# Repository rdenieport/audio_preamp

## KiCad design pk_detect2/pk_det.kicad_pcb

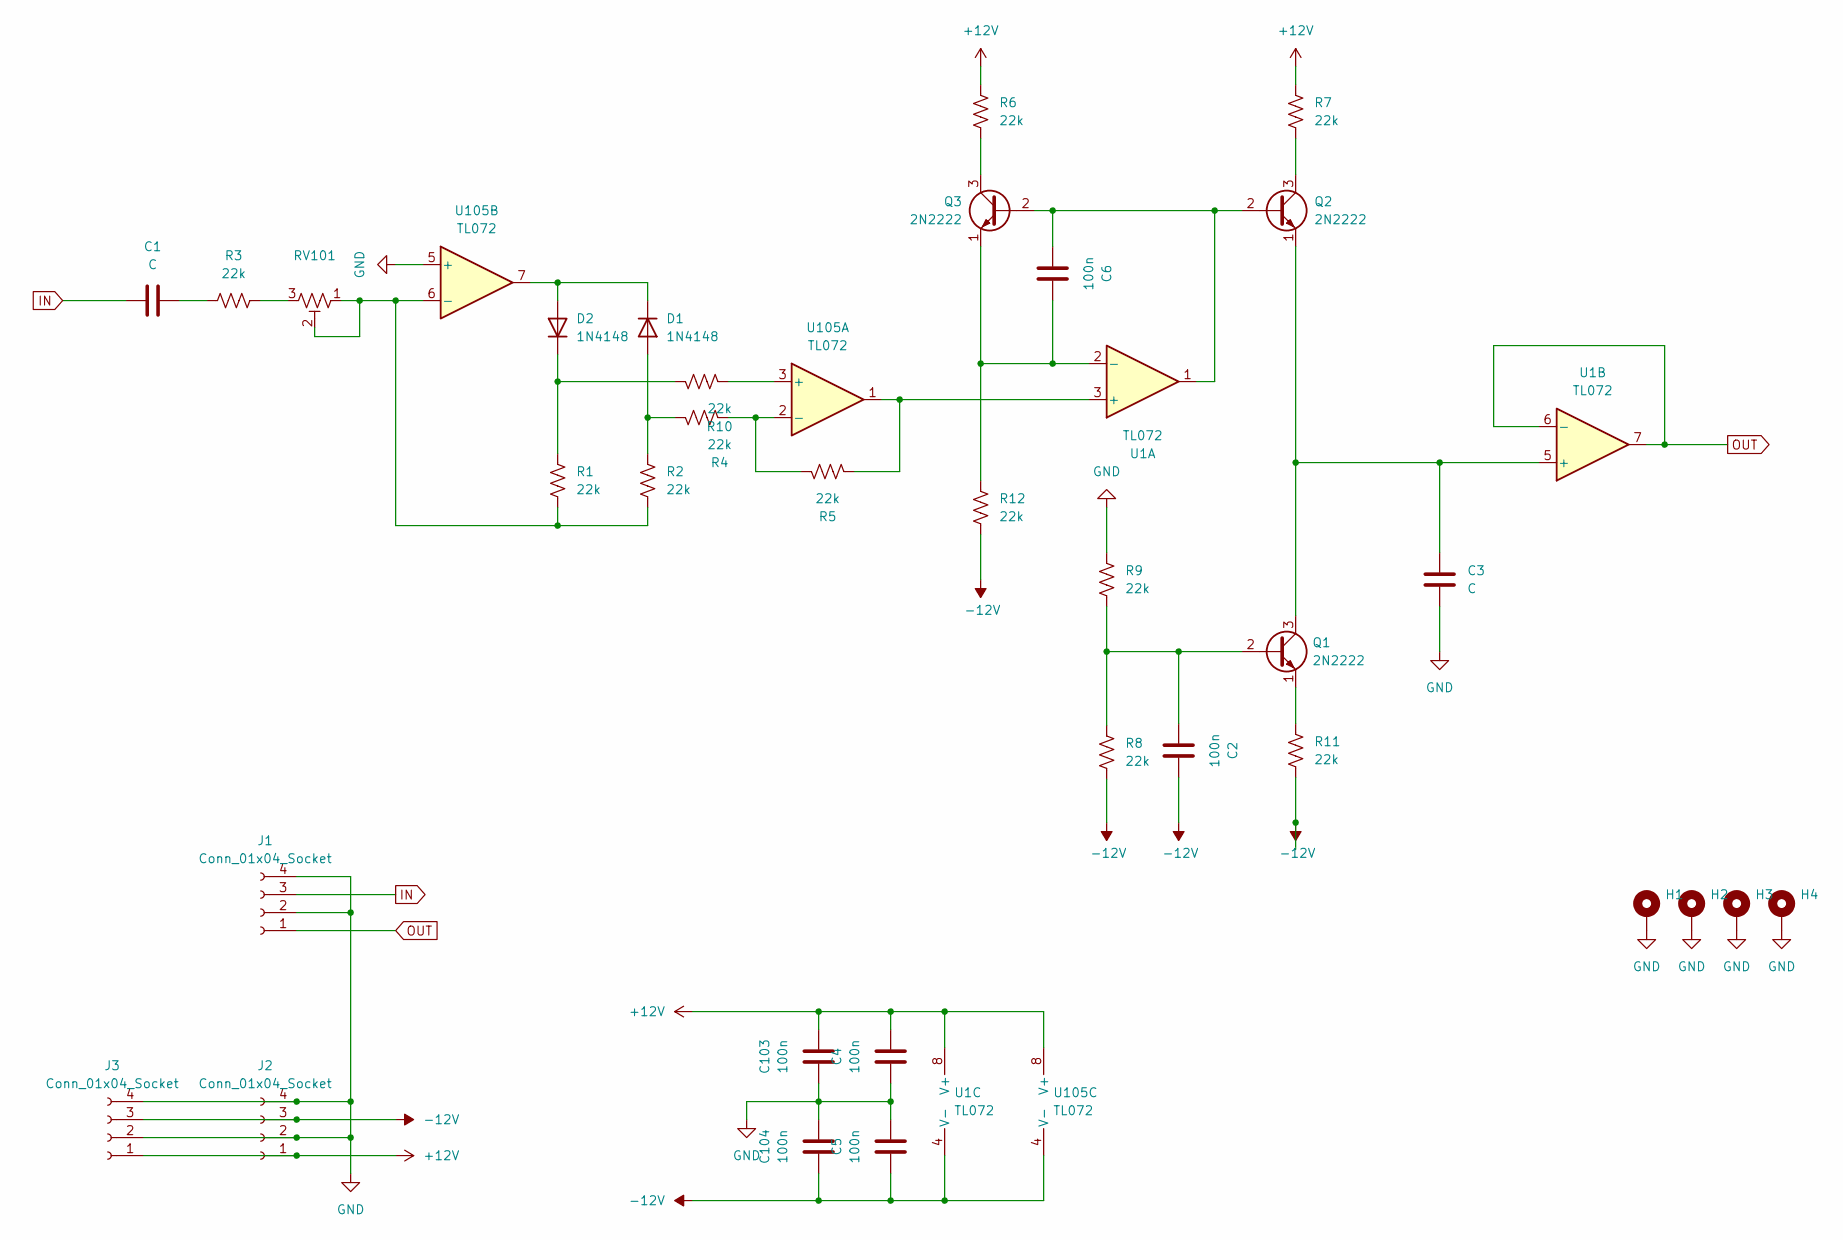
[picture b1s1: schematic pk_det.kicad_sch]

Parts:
C1, C3: C; C_Disc_D9.0mm_W5.0mm_P5.00mm
C2, C4, C5, C6, C103, C104: 100n; C_Disc_D4.3mm_W1.9mm_P5.00mm
D1, D2: 1N4148; D_DO-35_SOD27_P7.62mm_Horizontal
H1, H2, H3, H4: MountingHole_Pad_MP; MountingHole_3.2mm_M3_DIN965_Pad
J1, J2, J3: Conn_01x04_Socket; Molex_KK-254_AE-6410-04A_1x04_P2.54mm_Vertical
Q1, Q2, Q3: 2N2222; TO-46-3
R1, R2, R3, R4, R5, R6, R7, R8, R9, R10, R11, R12: 22k; R_Axial_DIN0207_L6.3mm_D2.5mm_P10.16mm_Horizontal
RV101: R_Potentiometer_Trim_US; Potentiometer_Bourns_3296W_Vertical
U1, U105: TL072; DIP-8_W7.62mm_LongPads

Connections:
+12V: C4.2, C103.2, J2.1, J3.1, R6.1, R7.1, U1.8 (V+), U105.8 (V+)
-12V: C2.1, C5.1, C104.1, J2.3, J3.3, R8.2, R11.2, R12.2, U1.4 (V-), U105.4 (V-)
GND: C3.1, C4.1, C5.2, C103.1, C104.2, H1.MP, H2.MP, H3.MP, H4.MP, J1.2, J1.4, J2.2, J2.4, J3.2, J3.4, R9.1, U105.5 (+)
IN: C1.1, J1.3
unnamed: C1.2, R3.1
unnamed: D1.2 (A), R2.1, R4.2
unnamed: D1.1 (K), D2.2 (A), U105.7
unnamed: D2.1 (K), R1.1, R10.2
unnamed: C2.2, Q1.2 (B), R8.1, R9.2
unnamed: C3.2, Q1.3 (C), Q2.1 (E), U1.5 (+)
unnamed: Q1.1 (E), R11.1
unnamed: C6.2, Q2.2 (B), Q3.2 (B), U1.1
unnamed: Q2.3 (C), R7.2
unnamed: Q3.3 (C), R6.2
unnamed: C6.1, Q3.1 (E), R12.1, U1.2 (-)
unnamed: R3.2, RV101.3
unnamed: R5.1, U1.3 (+), U105.1
unnamed: R10.1, U105.3 (+)
unnamed: R4.1, R5.2, U105.2 (-)
unnamed: R1.2, R2.2, RV101.1, RV101.2, U105.6 (-)
OUT: J1.1, U1.6 (-), U1.7

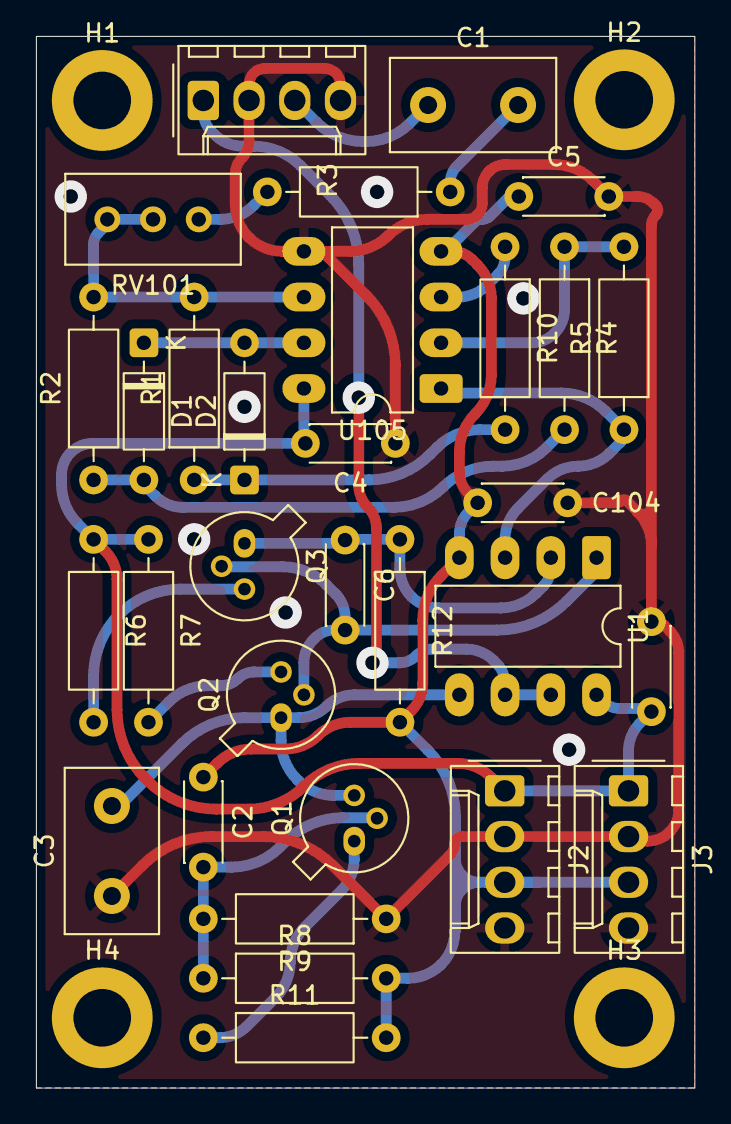
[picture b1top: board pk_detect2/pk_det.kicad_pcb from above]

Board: 2 copper layers, 36.6 x 58.4 mm, 35 parts (0 on the bottom side), 21 nets.

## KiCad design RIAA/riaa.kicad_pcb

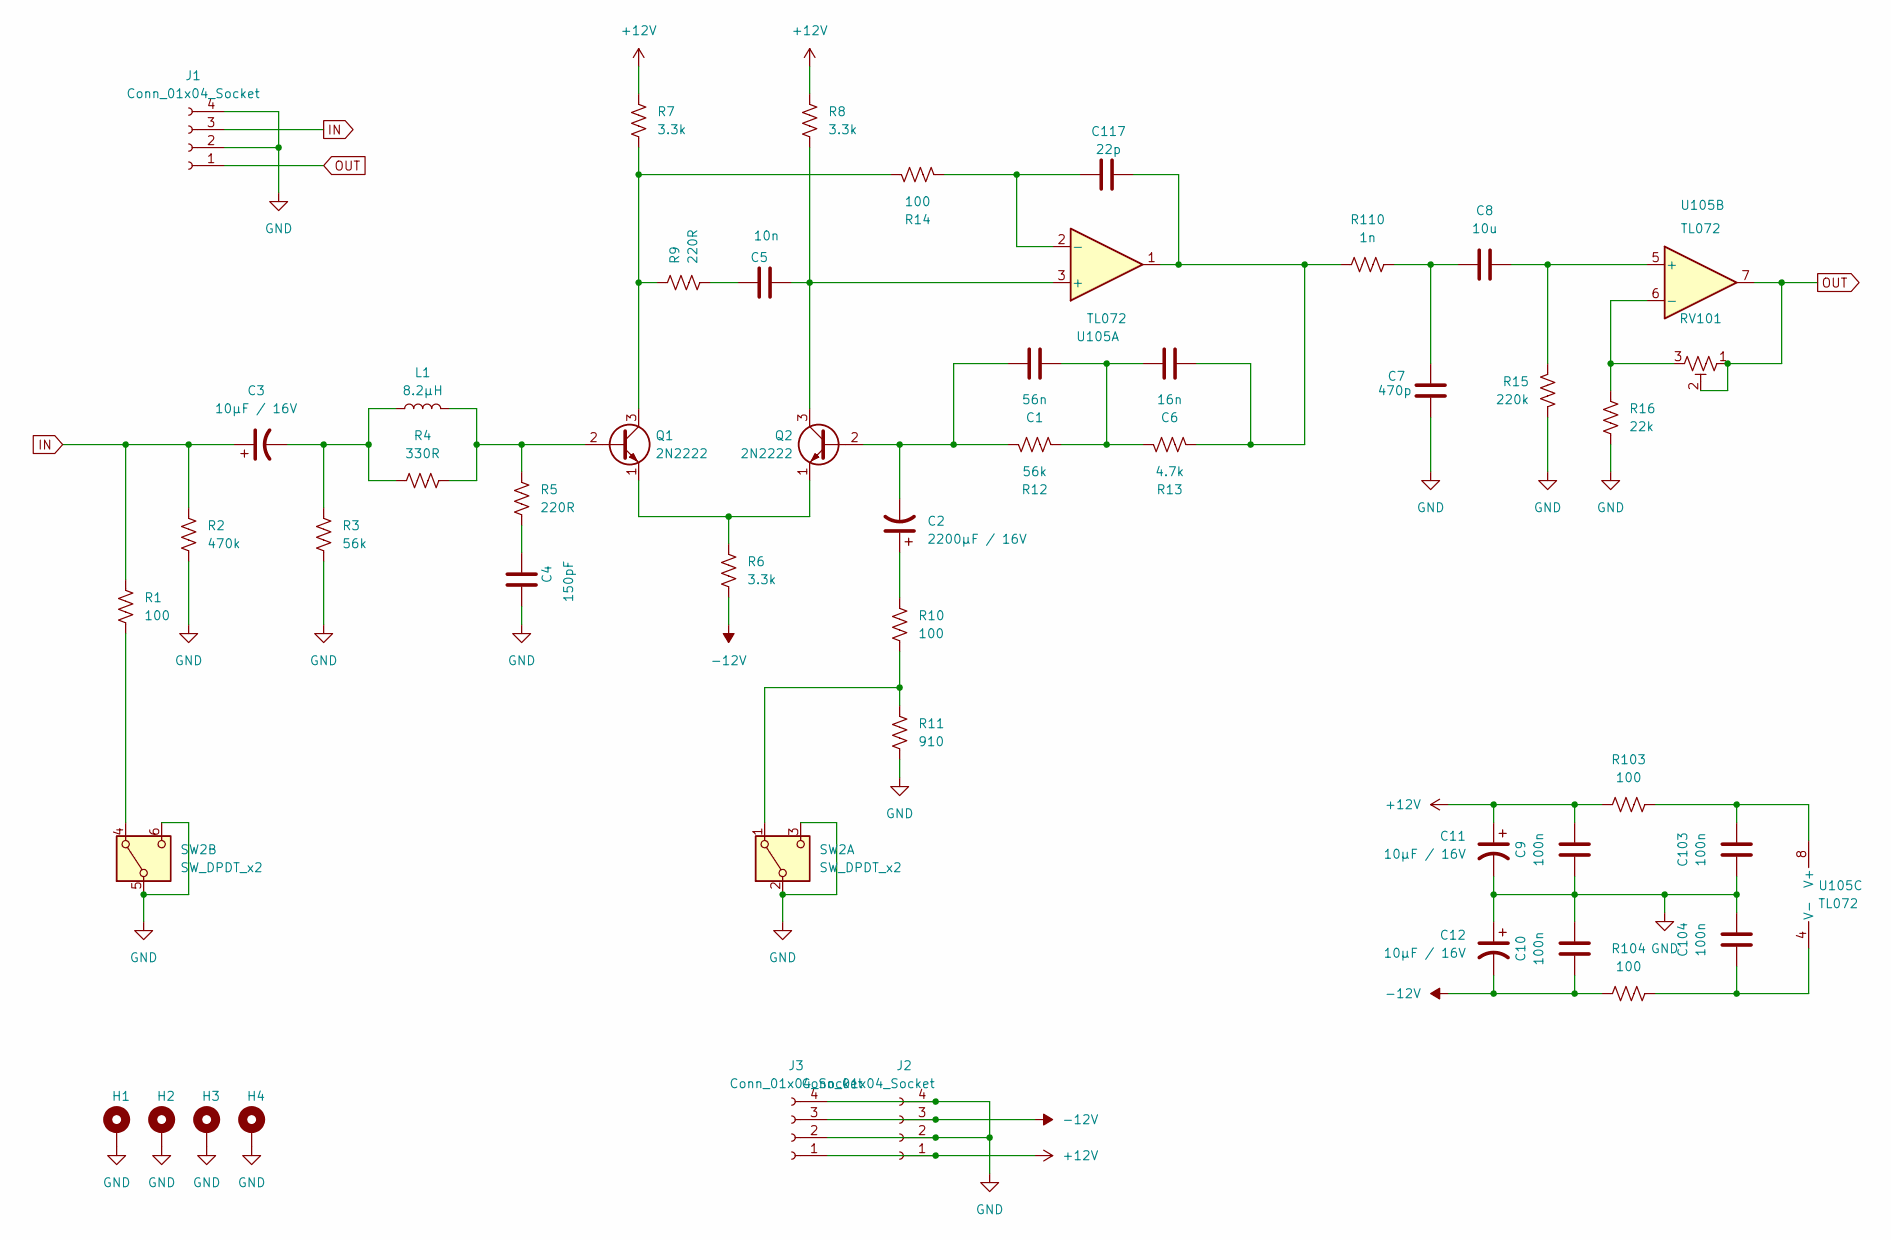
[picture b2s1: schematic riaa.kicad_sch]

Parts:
C1: 56n; C_Disc_D4.3mm_W1.9mm_P5.00mm
C2: 2200µF / 16V; CP_Radial_D8.0mm_P2.50mm
C3, C11, C12: 10µF / 16V; CP_Radial_D8.0mm_P2.50mm
C4: 150pF; C_Disc_D4.3mm_W1.9mm_P5.00mm
C5: 10n; C_Disc_D4.3mm_W1.9mm_P5.00mm
C6: 16n; C_Disc_D4.3mm_W1.9mm_P5.00mm
C7: 470p; C_Disc_D4.3mm_W1.9mm_P5.00mm
C8: 10u; C_Disc_D9.0mm_W5.0mm_P5.00mm
C9, C10, C103, C104: 100n; C_Disc_D4.3mm_W1.9mm_P5.00mm
C117: 22p; C_Disc_D4.3mm_W1.9mm_P5.00mm
H1, H2, H3, H4: MountingHole_Pad_MP; MountingHole_3.2mm_M3_DIN965_Pad
J1, J2, J3: Conn_01x04_Socket; Molex_KK-254_AE-6410-04A_1x04_P2.54mm_Vertical
L1: 8.2µH; L_Axial_L9.5mm_D4.0mm_P12.70mm_Horizontal_Fastron_SMCC
Q1, Q2: 2N2222; TO-46-3
R1, R10, R14, R103, R104: 100; R_Axial_DIN0207_L6.3mm_D2.5mm_P10.16mm_Horizontal
R2: 470k; R_Axial_DIN0207_L6.3mm_D2.5mm_P10.16mm_Horizontal
R3, R12: 56k; R_Axial_DIN0207_L6.3mm_D2.5mm_P10.16mm_Horizontal
R4: 330R; R_Axial_DIN0207_L6.3mm_D2.5mm_P10.16mm_Horizontal
R5, R9: 220R; R_Axial_DIN0207_L6.3mm_D2.5mm_P10.16mm_Horizontal
R6, R7, R8: 3.3k; R_Axial_DIN0207_L6.3mm_D2.5mm_P10.16mm_Horizontal
R11: 910; R_Axial_DIN0207_L6.3mm_D2.5mm_P10.16mm_Horizontal
R13: 4.7k; R_Axial_DIN0207_L6.3mm_D2.5mm_P10.16mm_Horizontal
R15: 220k; R_Axial_DIN0207_L6.3mm_D2.5mm_P10.16mm_Horizontal
R16: 22k; R_Axial_DIN0207_L6.3mm_D2.5mm_P10.16mm_Horizontal
R110: 1n; R_Axial_DIN0207_L6.3mm_D2.5mm_P10.16mm_Horizontal
RV101: R_Potentiometer_Trim_US; Potentiometer_Bourns_3296W_Vertical
SW2: SW_DPDT_x2; SW_PUSH_E-Switch_FS5700DP_DPDT
U105: TL072; DIP-8_W7.62mm_LongPads

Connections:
+12V: C9.2, C11.1, J2.1, J3.1, R7.1, R8.1, R103.1
-12V: C10.1, C12.2, J2.3, J3.3, R6.2, R104.1
GND: C4.1, C7.2, C9.1, C10.2, C11.2, C12.1, C103.1, C104.2, H1.1, H2.1, H3.1, H4.1, J1.2, J1.4, J2.2, J2.4, J3.2, J3.4, R2.2, R3.2, R11.2, R15.2, R16.2, SW2.2 (B), SW2.3 (C), SW2.5 (B), SW2.6 (C)
IN: C3.1, J1.3, R1.1, R2.1
unnamed: C1.1, C6.2, R12.2, R13.1
unnamed: C2.1, R10.1
unnamed: C3.2, L1.1, R3.1, R4.1
unnamed: C4.2, R5.2
unnamed: C5.2, R9.2
unnamed: C7.1, C8.2, R110.1
unnamed: C6.1, C117.2, R13.2, R110.2, U105.1
unnamed: L1.2, Q1.2 (B), R4.2, R5.1
unnamed: Q1.3 (C), R7.2, R9.1, R14.1
unnamed: Q1.1 (E), Q2.1 (E), R6.1
unnamed: C1.2, C2.2, Q2.2 (B), R12.1
unnamed: C5.1, Q2.3 (C), R8.2, U105.3 (+)
unnamed: R10.2, R11.1, SW2.1 (A)
unnamed: R1.2, SW2.4 (A)
unnamed: C117.1, R14.2, U105.2 (-)
unnamed: C8.1, R15.1, U105.5 (+)
unnamed: R16.1, RV101.3, U105.6 (-)
unnamed: C103.2, R103.2, U105.8 (V+)
unnamed: C104.1, R104.2, U105.4 (V-)
OUT: J1.1, RV101.1, RV101.2, U105.7

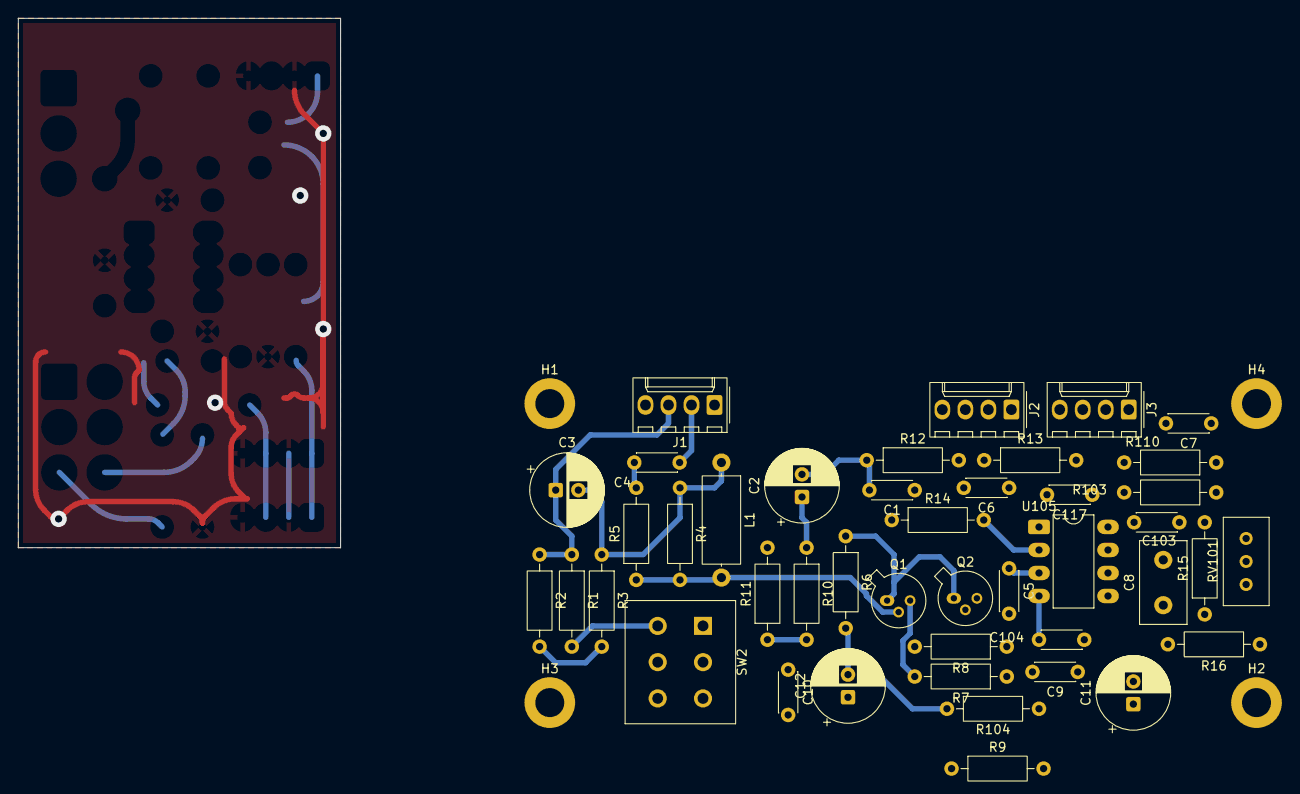
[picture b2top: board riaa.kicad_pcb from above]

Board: 2 copper layers, 35.6 x 58.4 mm, 47 parts (0 on the bottom side), 24 nets.

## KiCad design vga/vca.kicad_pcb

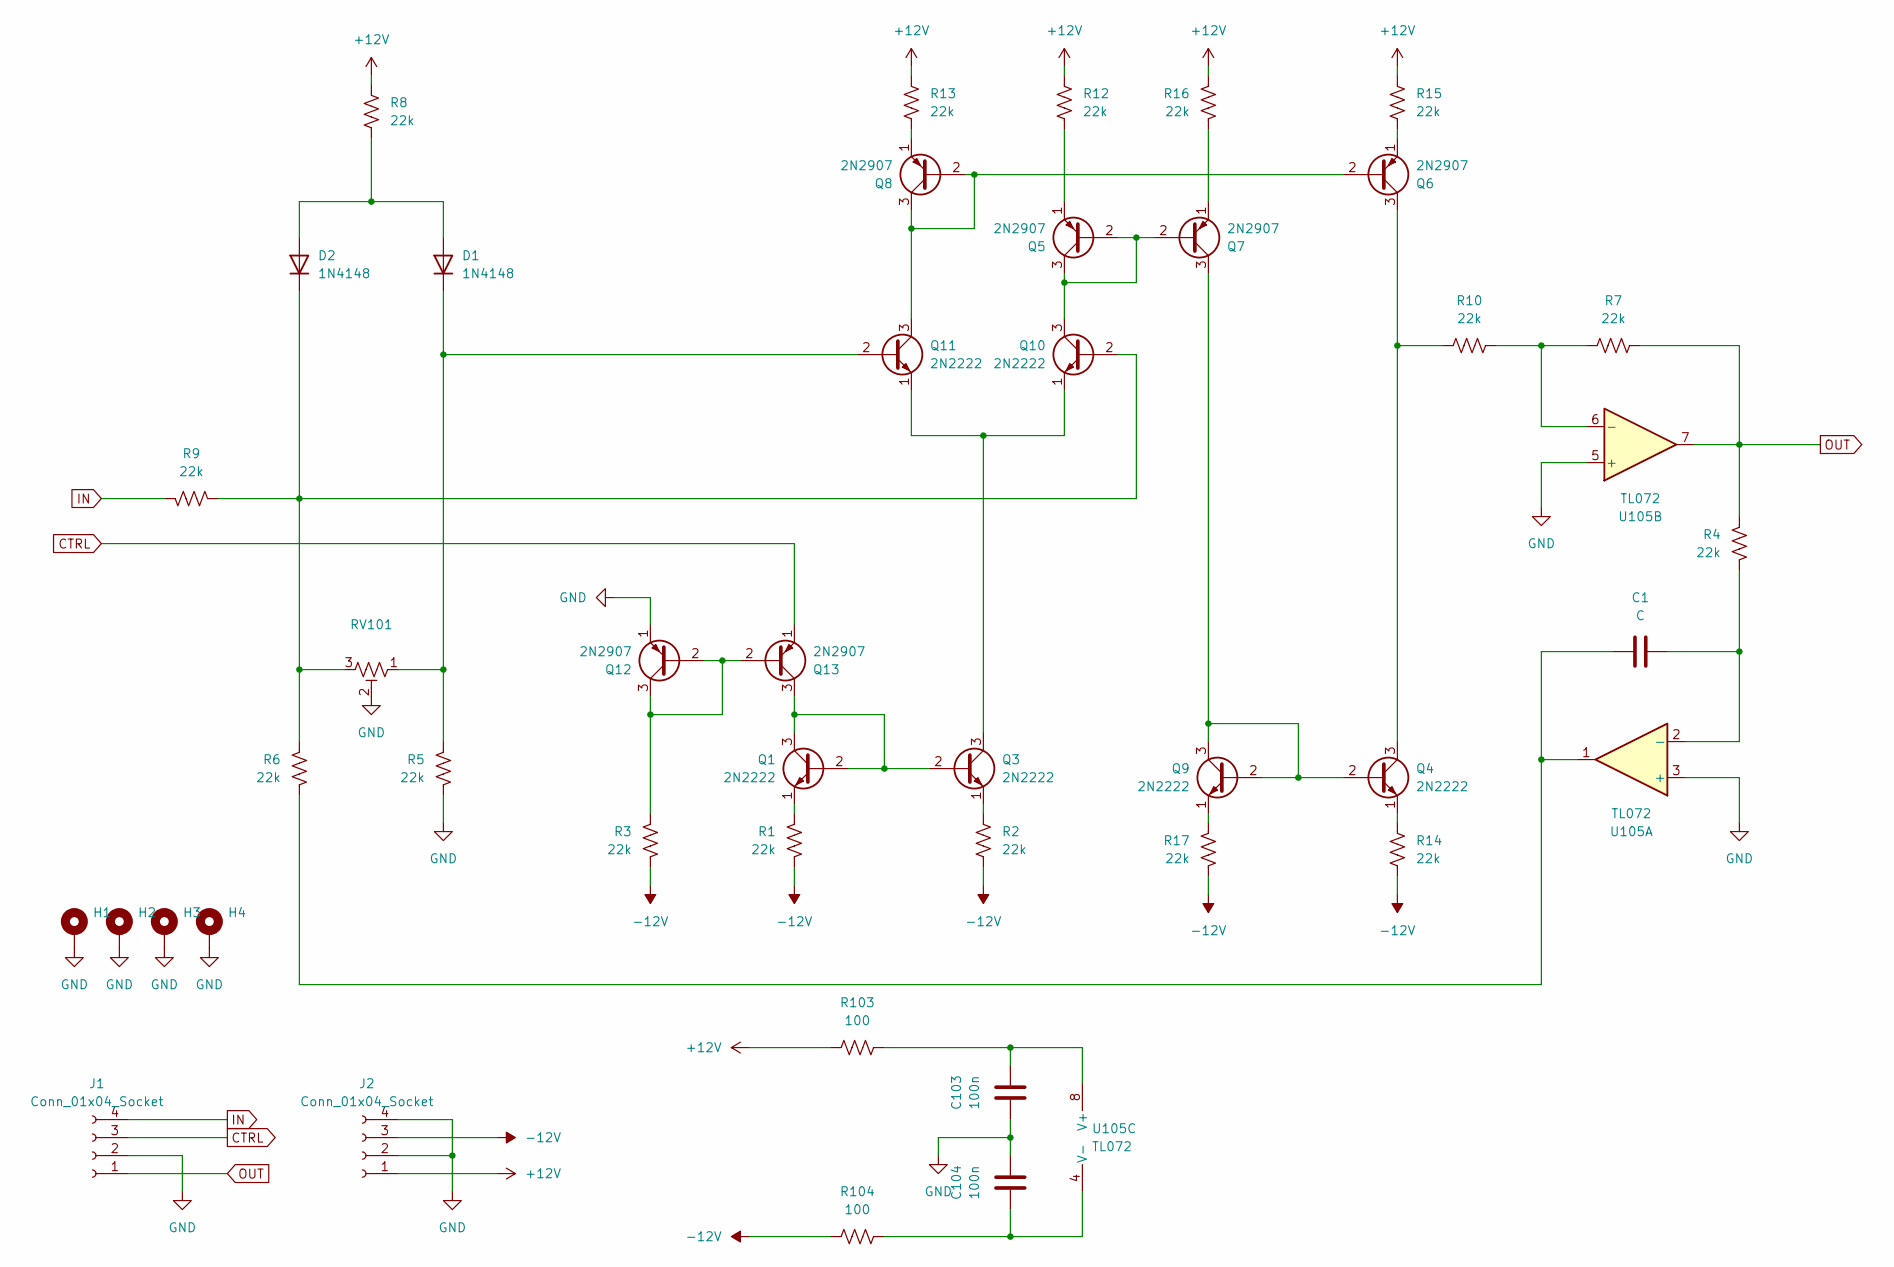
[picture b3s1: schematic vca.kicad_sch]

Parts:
C1: C; C_Disc_D9.0mm_W5.0mm_P5.00mm
C103, C104: 100n; C_Disc_D4.3mm_W1.9mm_P5.00mm
D1, D2: 1N4148; D_DO-35_SOD27_P7.62mm_Horizontal
H1, H2, H3, H4: MountingHole_Pad_MP; MountingHole_3.2mm_M3_DIN965_Pad
J1, J2: Conn_01x04_Socket; Molex_KK-254_AE-6410-04A_1x04_P2.54mm_Vertical
Q1, Q3, Q4, Q9, Q10, Q11: 2N2222; TO-46-3
Q5, Q6, Q7, Q8, Q12, Q13: 2N2907; TO-46-3
R1, R2, R3, R4, R5, R6, R7, R8, R9, R10, R12, R13, R14, R15, R16, R17: 22k; R_Axial_DIN0207_L6.3mm_D2.5mm_P10.16mm_Horizontal
R103, R104: 100; R_Axial_DIN0207_L6.3mm_D2.5mm_P10.16mm_Horizontal
RV101: R_Potentiometer_Trim_US; Potentiometer_Bourns_3296W_Vertical
U105: TL072; DIP-8_W7.62mm_LongPads

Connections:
+12V: J2.1, R8.1, R12.1, R13.1, R15.1, R16.1, R103.1; also elsewhere on the board
-12V: J2.3, R1.2, R2.2, R3.2, R14.2, R17.2, R104.1; also elsewhere on the board
CTRL: J1.3, Q13.1 (E)
GND: C103.1, C104.2, H1.1, H1.MP, H2.1, H2.MP, H3.1, H3.MP, H4.1, H4.MP, J1.2, J2.2, J2.4, Q12.1 (E), R5.2, RV101.2, U105.3 (+), U105.5 (+); also elsewhere on the board
IN: J1.4, R9.1
unnamed: C1.1, R6.2, U105.1
unnamed: Q1.2 (B), Q1.3 (C), Q3.2 (B), Q13.3 (C)
unnamed: Q1.1 (E), R1.1
unnamed: Q3.1 (E), R2.1
unnamed: Q4.2 (B), Q7.3 (C), Q9.2 (B), Q9.3 (C)
unnamed: Q4.3 (C), Q6.3 (C), R10.1
unnamed: Q4.1 (E), R14.1
unnamed: Q5.1 (E), R12.2
unnamed: Q6.1 (E), R15.2
unnamed: Q7.1 (E), R16.2
unnamed: Q8.1 (E), R13.2
unnamed: Q9.1 (E), R17.1
unnamed 17: D2.1 (K), Q10.2 (B), R6.1, R9.2, RV101.3; also elsewhere on the board
unnamed: Q5.2 (B), Q5.3 (C), Q7.2 (B), Q10.3 (C)
unnamed: Q3.3 (C), Q10.1 (E), Q11.1 (E)
unnamed 20: D1.1 (K), Q11.2 (B), R5.1, RV101.1; also elsewhere on the board
unnamed: Q6.2 (B), Q8.2 (B), Q8.3 (C), Q11.3 (C)
unnamed: Q12.2 (B), Q12.3 (C), Q13.2 (B), R3.1
unnamed 23: D1.2 (A), D2.2 (A), R8.2; also elsewhere on the board
unnamed: C1.2, R4.2, U105.2 (-)
unnamed: R7.1, R10.2, U105.6 (-)
unnamed: C103.2, R103.2, U105.8 (V+)
unnamed: C104.1, R104.2, U105.4 (V-)
OUT: J1.1, R4.1, R7.2, U105.7

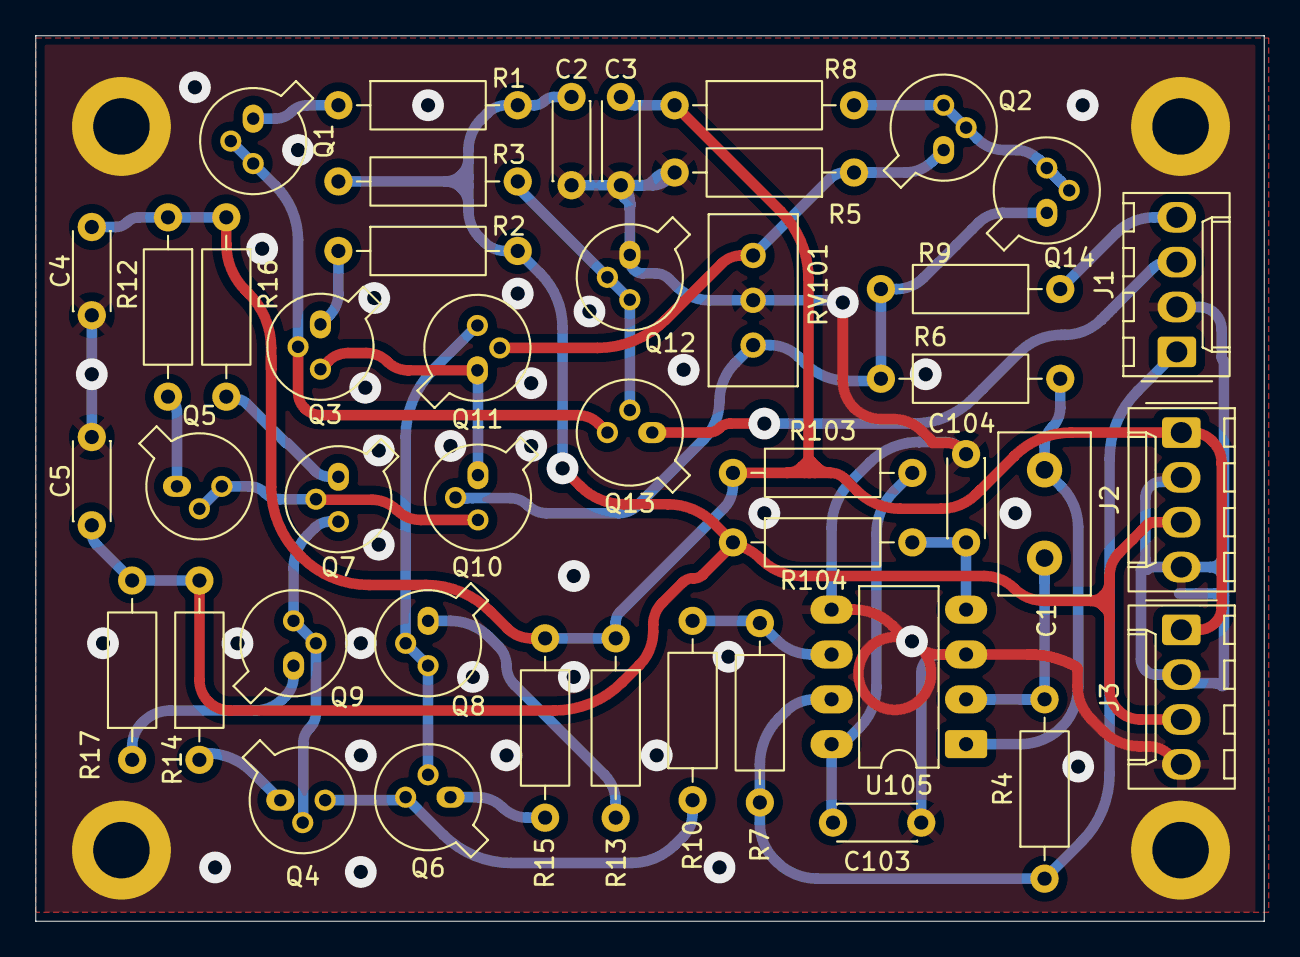
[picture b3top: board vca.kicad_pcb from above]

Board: 2 copper layers, 69.6 x 50.2 mm, 48 parts (0 on the bottom side), 29 nets.

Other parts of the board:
C2, C3, C4, C5: 100n; C_Disc_D4.3mm_W1.9mm_P5.00mm
J3: Conn_01x04_Socket; Molex_KK-254_AE-6410-04A_1x04_P2.54mm_Vertical
Q2, Q14: 2N2222; TO-46-3

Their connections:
+12V: C2.2, C4.2, J3.1; also elsewhere on the board
-12V: C3.1, C5.1, J3.3; also elsewhere on the board
GND: C2.1, C3.2, C4.1, C5.2, J3.2, J3.4; also elsewhere on the board
unnamed 17: Q14.1 (E); also elsewhere on the board
unnamed 20: Q2.1 (E); also elsewhere on the board
unnamed 23: Q2.2 (B), Q2.3 (C), Q14.2 (B), Q14.3 (C); also elsewhere on the board

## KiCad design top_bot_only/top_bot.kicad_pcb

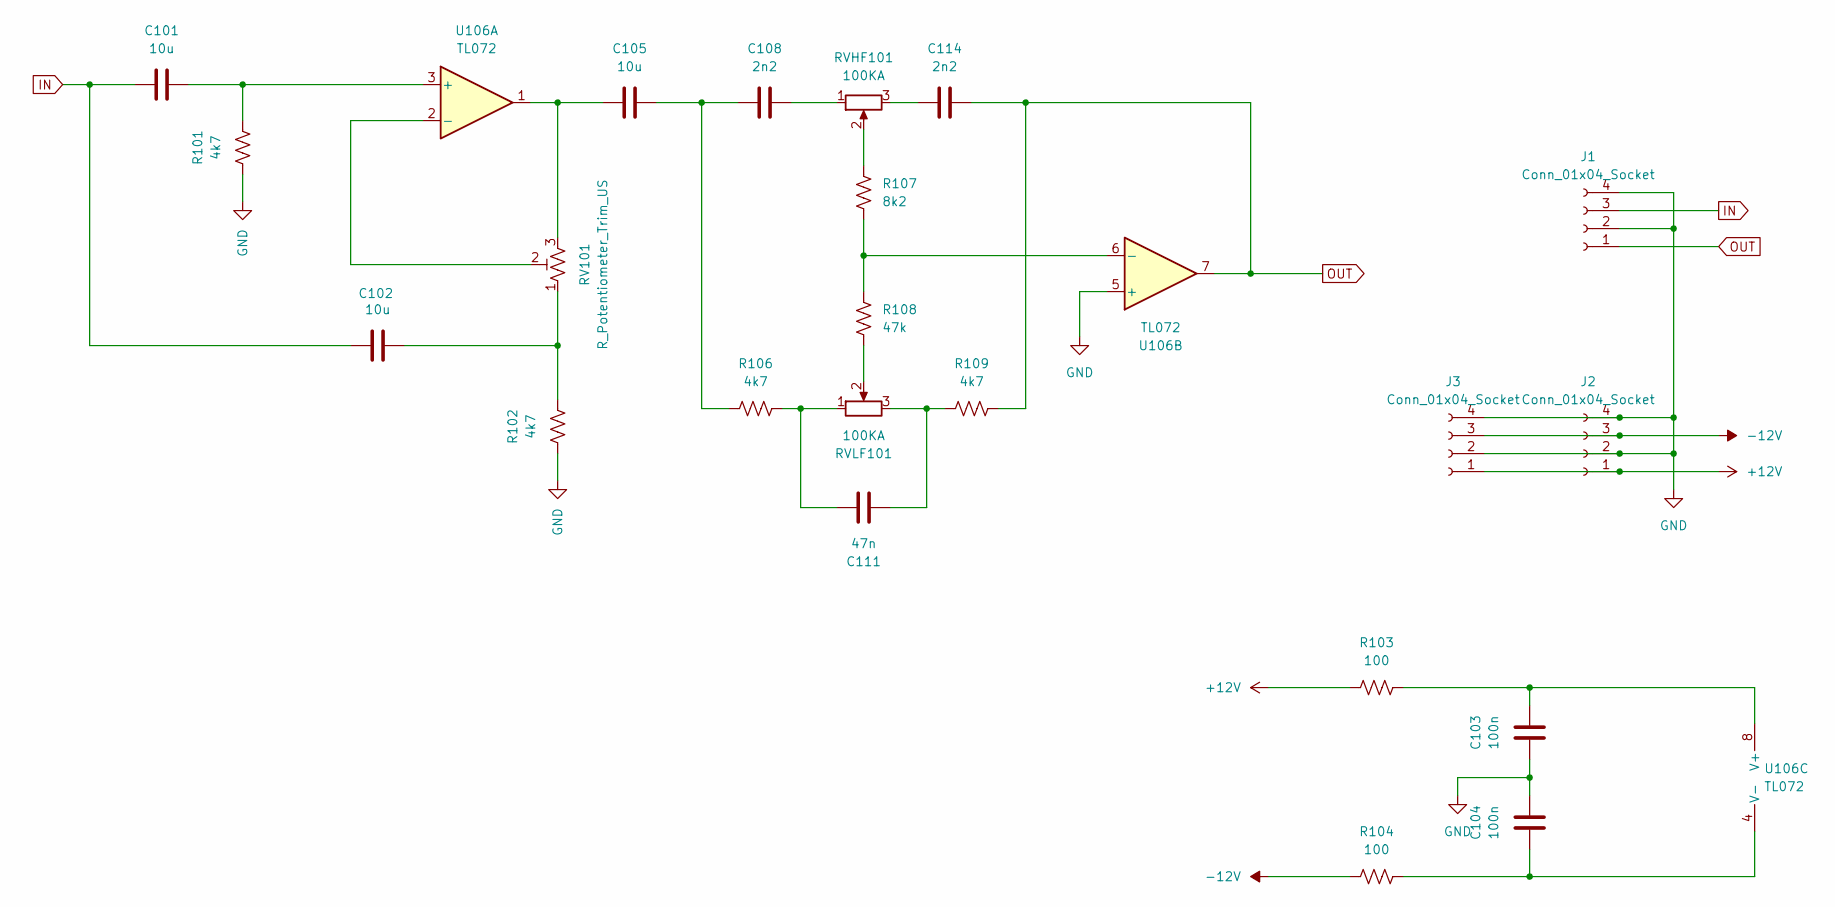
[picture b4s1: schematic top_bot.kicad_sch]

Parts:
C101, C102, C105: 10u; C_Disc_D4.3mm_W1.9mm_P5.00mm
C103, C104: 100n; C_Disc_D4.3mm_W1.9mm_P5.00mm
C108, C114: 2n2; C_Disc_D4.3mm_W1.9mm_P5.00mm
C111: 47n; C_Disc_D4.3mm_W1.9mm_P5.00mm
J1, J2, J3: Conn_01x04_Socket; Molex_KK-254_AE-6410-04A_1x04_P2.54mm_Vertical
R101, R102, R106, R109: 4k7; R_Axial_DIN0207_L6.3mm_D2.5mm_P10.16mm_Horizontal
R103, R104: 100; R_Axial_DIN0207_L6.3mm_D2.5mm_P10.16mm_Horizontal
R107: 8k2; R_Axial_DIN0207_L6.3mm_D2.5mm_P10.16mm_Horizontal
R108: 47k; R_Axial_DIN0207_L6.3mm_D2.5mm_P10.16mm_Horizontal
RV101: R_Potentiometer_Trim_US; Potentiometer_Bourns_3296W_Vertical
RVHF101: 100KA; Potentiometer_Alps_RK163_Single_Horizontal
RVLF101: 100KA; Potentiometer_Alps_RK163_Single_Horizontal
U106: TL072; DIP-8_W7.62mm_LongPads

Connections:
+12V: J2.1, J3.1, R103.1
-12V: J2.3, J3.3, R104.1
GND: C103.1, C104.2, J1.2, J1.4, J2.2, J2.4, J3.2, J3.4, R101.1, R102.1, U106.5 (+)
IN: C101.1, C102.1, J1.3
unnamed: C102.2, R102.2, RV101.1
unnamed: C105.1, RV101.3, U106.1
unnamed: C105.2, C108.1, R106.1
unnamed: C108.2, RVHF101.1
unnamed: C111.1, R106.2, RVLF101.1
unnamed: C111.2, R109.1, RVLF101.3
unnamed: C114.1, RVHF101.3
unnamed: R107.2, RVHF101.2
unnamed: R108.1, RVLF101.2
unnamed: C101.2, R101.2, U106.3 (+)
unnamed: RV101.2, U106.2 (-)
unnamed: R107.1, R108.2, U106.6 (-)
unnamed: C103.2, R103.2, U106.8 (V+)
unnamed: C104.1, R104.2, U106.4 (V-)
OUT: C114.2, J1.1, R109.2, U106.7

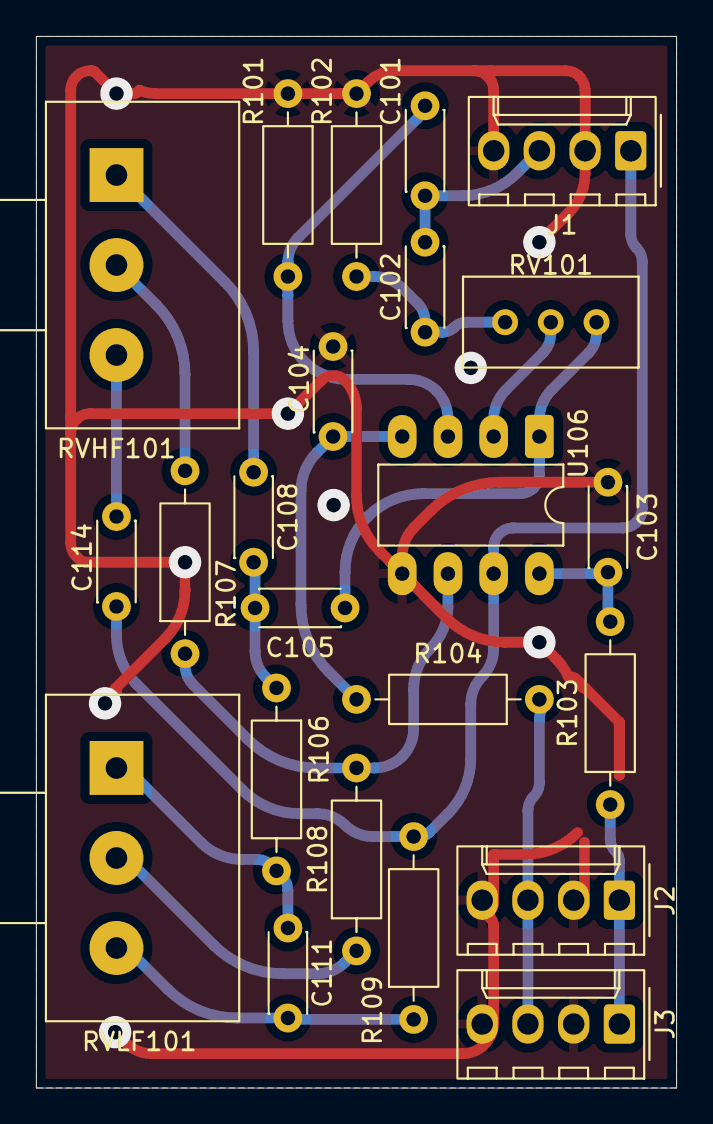
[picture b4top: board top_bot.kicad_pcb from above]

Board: 2 copper layers, 35.6 x 58.4 mm, 23 parts (0 on the bottom side), 19 nets.

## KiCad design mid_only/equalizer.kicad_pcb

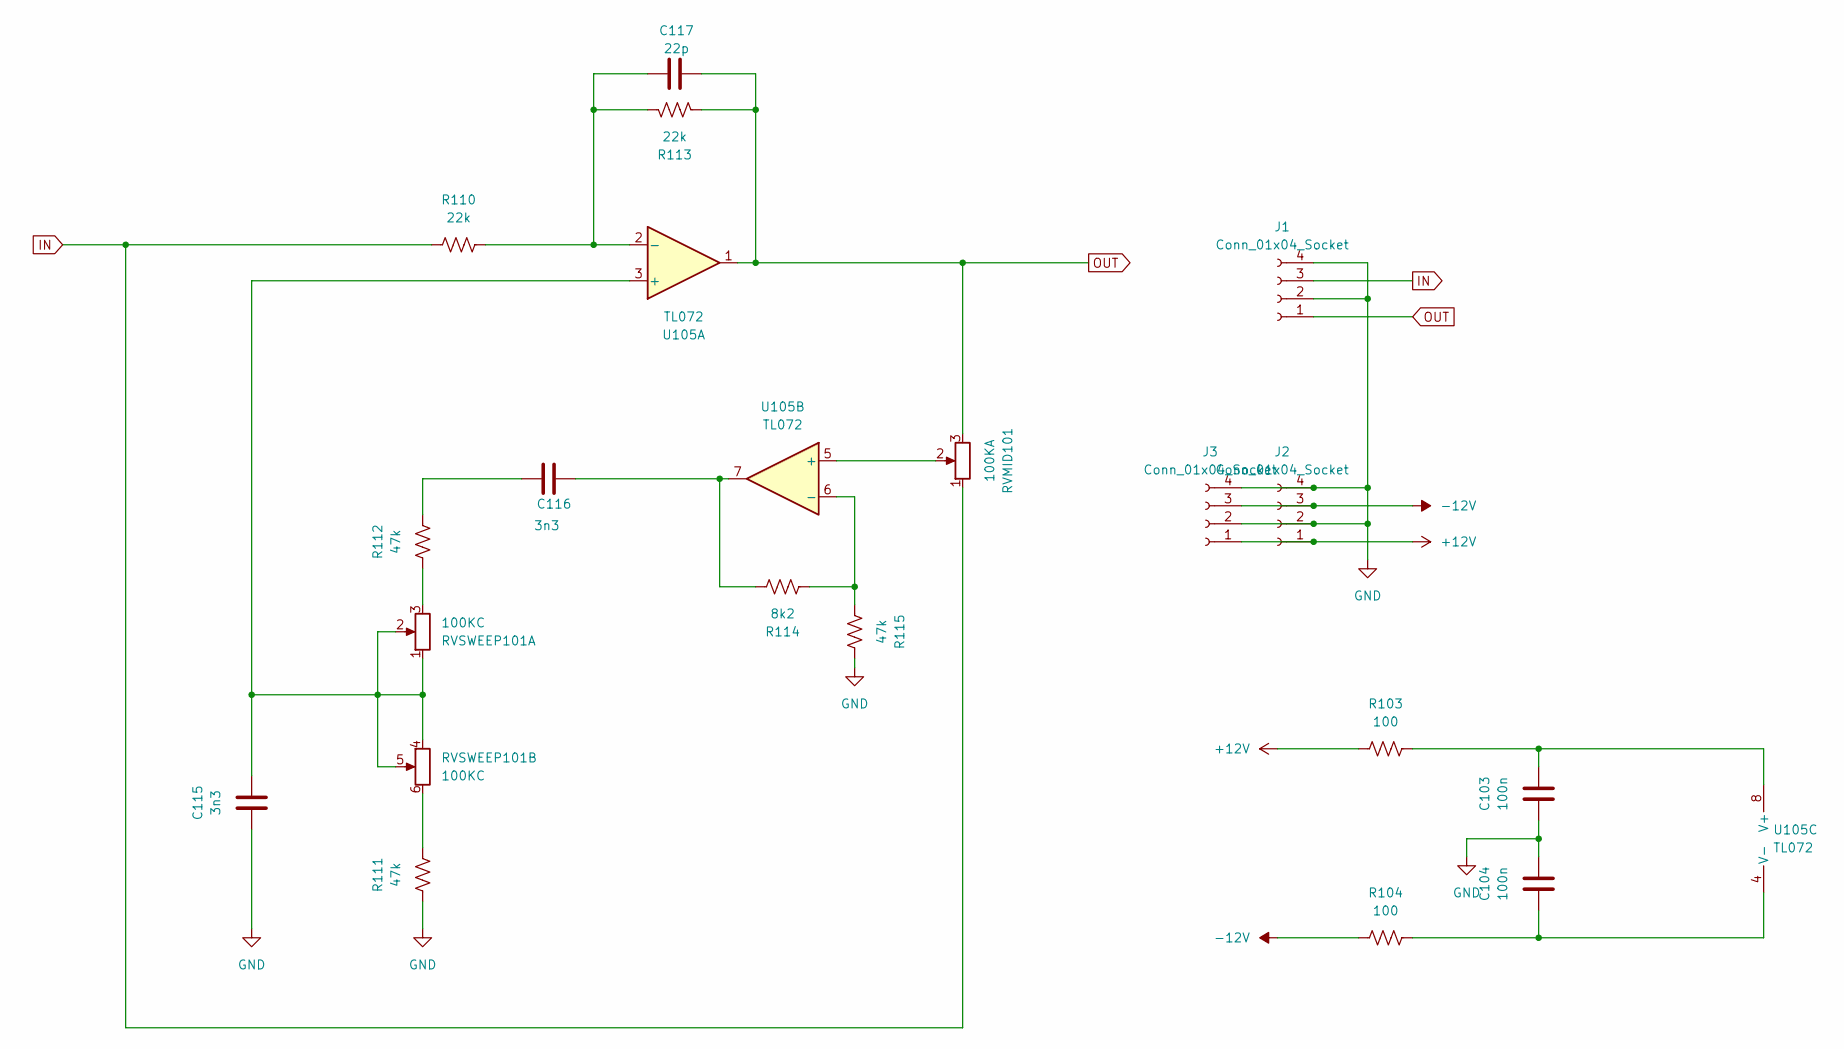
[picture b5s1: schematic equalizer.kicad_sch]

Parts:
C103, C104: 100n; C_Disc_D4.3mm_W1.9mm_P5.00mm
C115, C116: 3n3; C_Disc_D4.3mm_W1.9mm_P5.00mm
C117: 22p; C_Disc_D4.3mm_W1.9mm_P5.00mm
J1, J2, J3: Conn_01x04_Socket; Molex_KK-254_AE-6410-04A_1x04_P2.54mm_Vertical
R103, R104: 100; R_Axial_DIN0207_L6.3mm_D2.5mm_P10.16mm_Horizontal
R110, R113: 22k; R_Axial_DIN0207_L6.3mm_D2.5mm_P10.16mm_Horizontal
R111, R112, R115: 47k; R_Axial_DIN0207_L6.3mm_D2.5mm_P10.16mm_Horizontal
R114: 8k2; R_Axial_DIN0207_L6.3mm_D2.5mm_P10.16mm_Horizontal
RVMID101: 100KA; Potentiometer_Alps_RK163_Single_Horizontal
RVSWEEP101: 100KC; Potentiometer_Alps_RK163_Dual_Horizontal
U105: TL072; DIP-8_W7.62mm_LongPads

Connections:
+12V: J2.1, J3.1, R103.1
-12V: J2.3, J3.3, R104.1
GND: C103.1, C104.2, C115.1, J1.2, J1.4, J2.2, J2.4, J3.2, J3.4, R111.2, R115.1
IN: J1.3, R110.2, RVMID101.1
unnamed: C116.1, R112.1
unnamed: C116.2, R114.1, U105.7
unnamed: R111.1, RVSWEEP101.6
unnamed: R112.2, RVSWEEP101.3
unnamed: C115.2, RVSWEEP101.1, RVSWEEP101.2, RVSWEEP101.4, RVSWEEP101.5, U105.3 (+)
unnamed: C117.1, R110.1, R113.2, U105.2 (-)
unnamed: RVMID101.2, U105.5 (+)
unnamed: R114.2, R115.2, U105.6 (-)
unnamed: C103.2, R103.2, U105.8 (V+)
unnamed: C104.1, R104.2, U105.4 (V-)
OUT: C117.2, J1.1, R113.1, RVMID101.3, U105.1

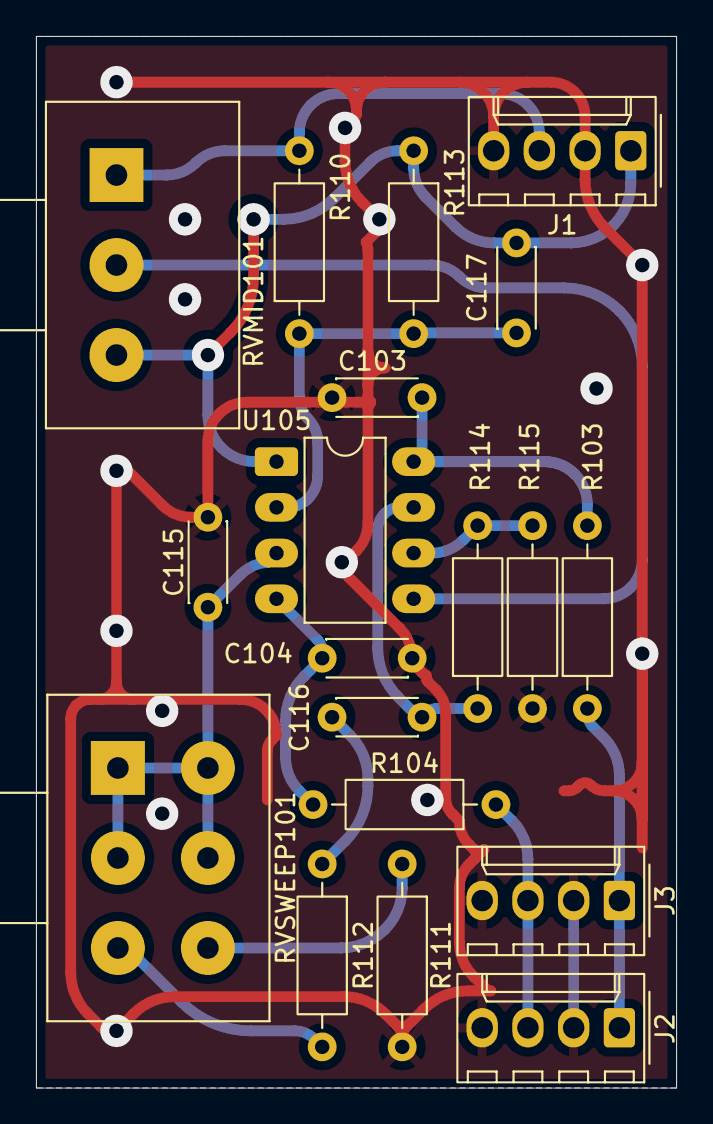
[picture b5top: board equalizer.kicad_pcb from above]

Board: 2 copper layers, 35.6 x 58.4 mm, 19 parts (0 on the bottom side), 15 nets.
